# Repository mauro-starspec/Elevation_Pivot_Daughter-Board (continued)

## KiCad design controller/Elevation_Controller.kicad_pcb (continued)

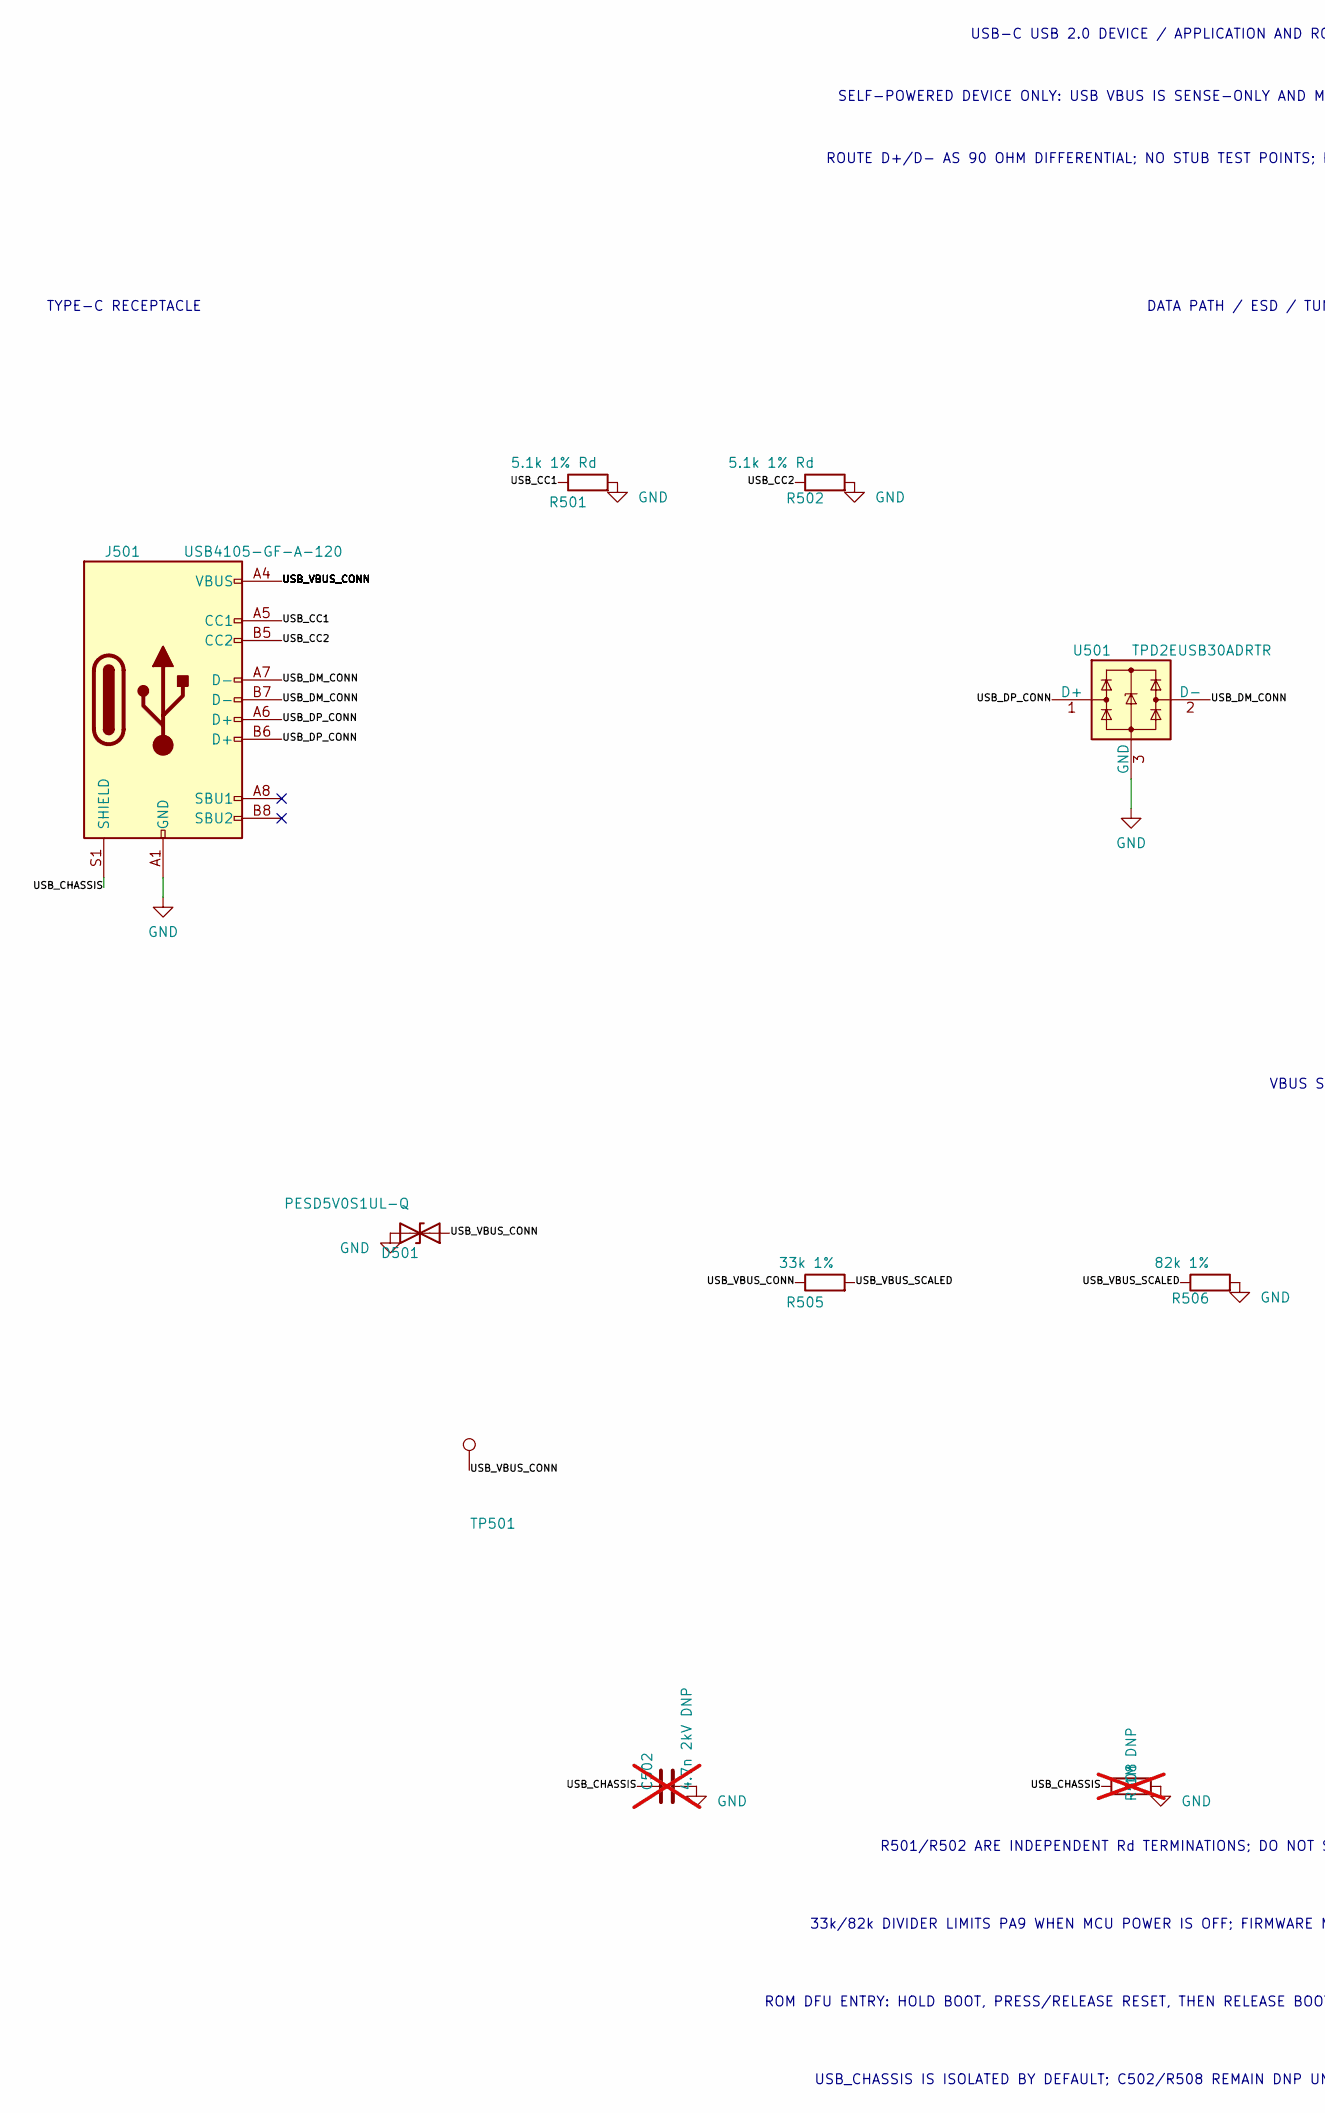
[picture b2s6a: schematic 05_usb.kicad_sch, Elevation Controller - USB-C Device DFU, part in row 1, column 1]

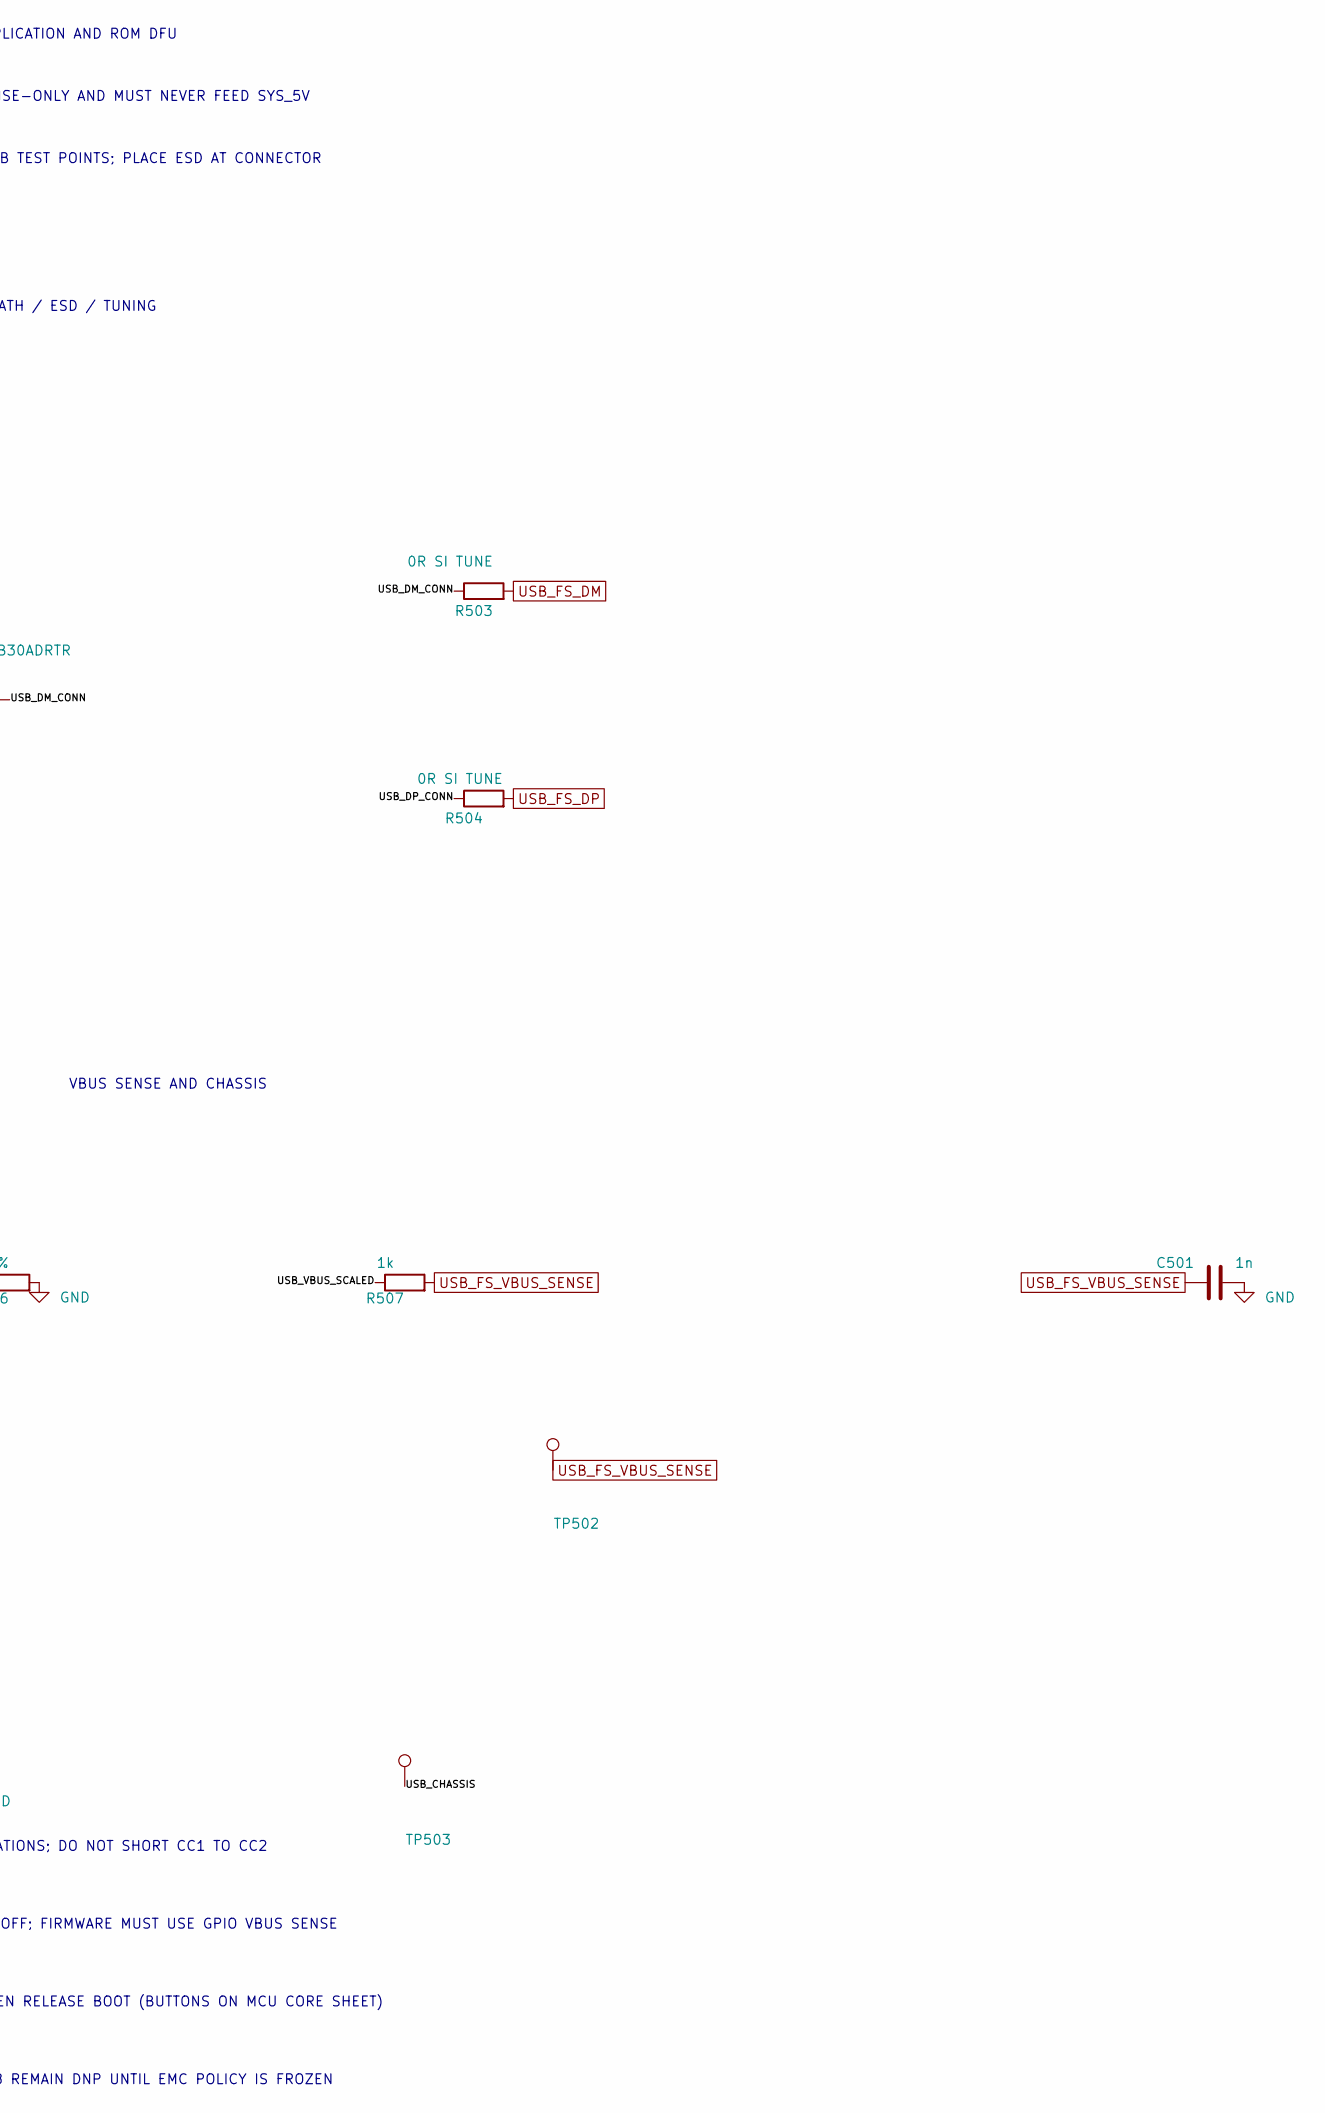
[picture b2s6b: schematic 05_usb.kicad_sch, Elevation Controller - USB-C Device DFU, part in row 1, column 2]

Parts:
C501: 1n; C_0805_2012Metric; Voltage 50V; MPN C0805C102J5GACTU; LCSC Part # C2167084
C502: 4.7n 2kV DNP; C_1812_4532Metric; MPN NOT SELECTED - DNP; LCSC Part # NOT_SELECTED; not fitted
D501: PESD5V0S1UL-Q; D_SOD-882; MPN PESD5V0S1UL-QYL; LCSC Part # C20235797
J501: USB4105-GF-A-120; USB_C_Receptacle_GCT_USB4105-xx-A_16P_TopMnt_Horizontal; MPN USB4105-GF-A-120; LCSC Part # C5184243
R501, R502: 5.1k 1% Rd; R_0805_2012Metric; MPN CRCW08055K10FKEA; LCSC Part # C844854
R503, R504: 0R SI TUNE; R_0805_2012Metric; MPN CRCW08050000Z0EA; LCSC Part # C844934
R505: 33k 1%; R_0805_2012Metric; MPN CRCW080533K0FKEA; LCSC Part # C242487
R506: 82k 1%; R_0805_2012Metric; MPN CRCW080582K0FKEA; LCSC Part # NOT_LISTED
R507: 1k; R_0805_2012Metric; MPN CRCW08051K00FKEA; LCSC Part # C844939
R508: 1M DNP; R_0805_2012Metric; MPN NOT SELECTED - DNP; LCSC Part # NOT_SELECTED; not fitted
TP501: USB_VBUS_CONN; TestPoint_Pad_D2.0mm; MPN N/A; LCSC Part # N/A
TP502: USB_FS_VBUS_SENSE; TestPoint_Pad_D2.0mm; MPN N/A; LCSC Part # N/A
TP503: USB_CHASSIS; TestPoint_Pad_D2.0mm; MPN N/A; LCSC Part # N/A
U501: TPD2EUSB30ADRTR; Texas_DRT-3; MPN TPD2EUSB30ADRTR; LCSC Part # C94934

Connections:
/USB-C/USB_CC1: J501.A5 (CC1), R501.1
/USB-C/USB_CC2: J501.B5 (CC2), R502.1
/USB-C/USB_CHASSIS: C502.1, J501.S1 (SHIELD), R508.1, TP503.1
/USB-C/USB_DM_CONN: J501.A7 (D-), J501.B7 (D-), R503.1, U501.2 (D-)
/USB-C/USB_DP_CONN: J501.A6 (D+), J501.B6 (D+), R504.1, U501.1 (D+)
/USB-C/USB_VBUS_CONN: D501.1 (A1), J501.A4 (VBUS), J501.A9 (VBUS), J501.B4 (VBUS), J501.B9 (VBUS), R505.1, TP501.1
/USB-C/USB_VBUS_SCALED: R505.2, R506.1, R507.1
GND: C501.2, C502.2, D501.2 (A2), J501.A1 (GND), J501.A12 (GND), J501.B1 (GND), J501.B12 (GND), R501.2, R502.2, R506.2, R508.2, U501.3 (GND); also elsewhere on the board
USB_FS_DM: R503.2; also elsewhere on the board
USB_FS_DP: R504.2; also elsewhere on the board
USB_FS_VBUS_SENSE: C501.1, R507.2, TP502.1; also elsewhere on the board

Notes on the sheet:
33k/82k DIVIDER LIMITS PA9 WHEN MCU POWER IS OFF; FIRMWARE MUST USE GPIO VBUS SENSE
DATA PATH / ESD / TUNING
VBUS SENSE AND CHASSIS
ROUTE D+/D- AS 90 OHM DIFFERENTIAL; NO STUB TEST POINTS; PLACE ESD AT CONNECTOR
TYPE-C RECEPTACLE
R501/R502 ARE INDEPENDENT Rd TERMINATIONS; DO NOT SHORT CC1 TO CC2
SELF-POWERED DEVICE ONLY: USB VBUS IS SENSE-ONLY AND MUST NEVER FEED SYS_5V
USB-C USB 2.0 DEVICE / APPLICATION AND ROM DFU
ROM DFU ENTRY: HOLD BOOT, PRESS/RELEASE RESET, THEN RELEASE BOOT (BUTTONS ON MCU CORE SHEET)
USB_CHASSIS IS ISOLATED BY DEFAULT; C502/R508 REMAIN DNP UNTIL EMC POLICY IS FROZEN

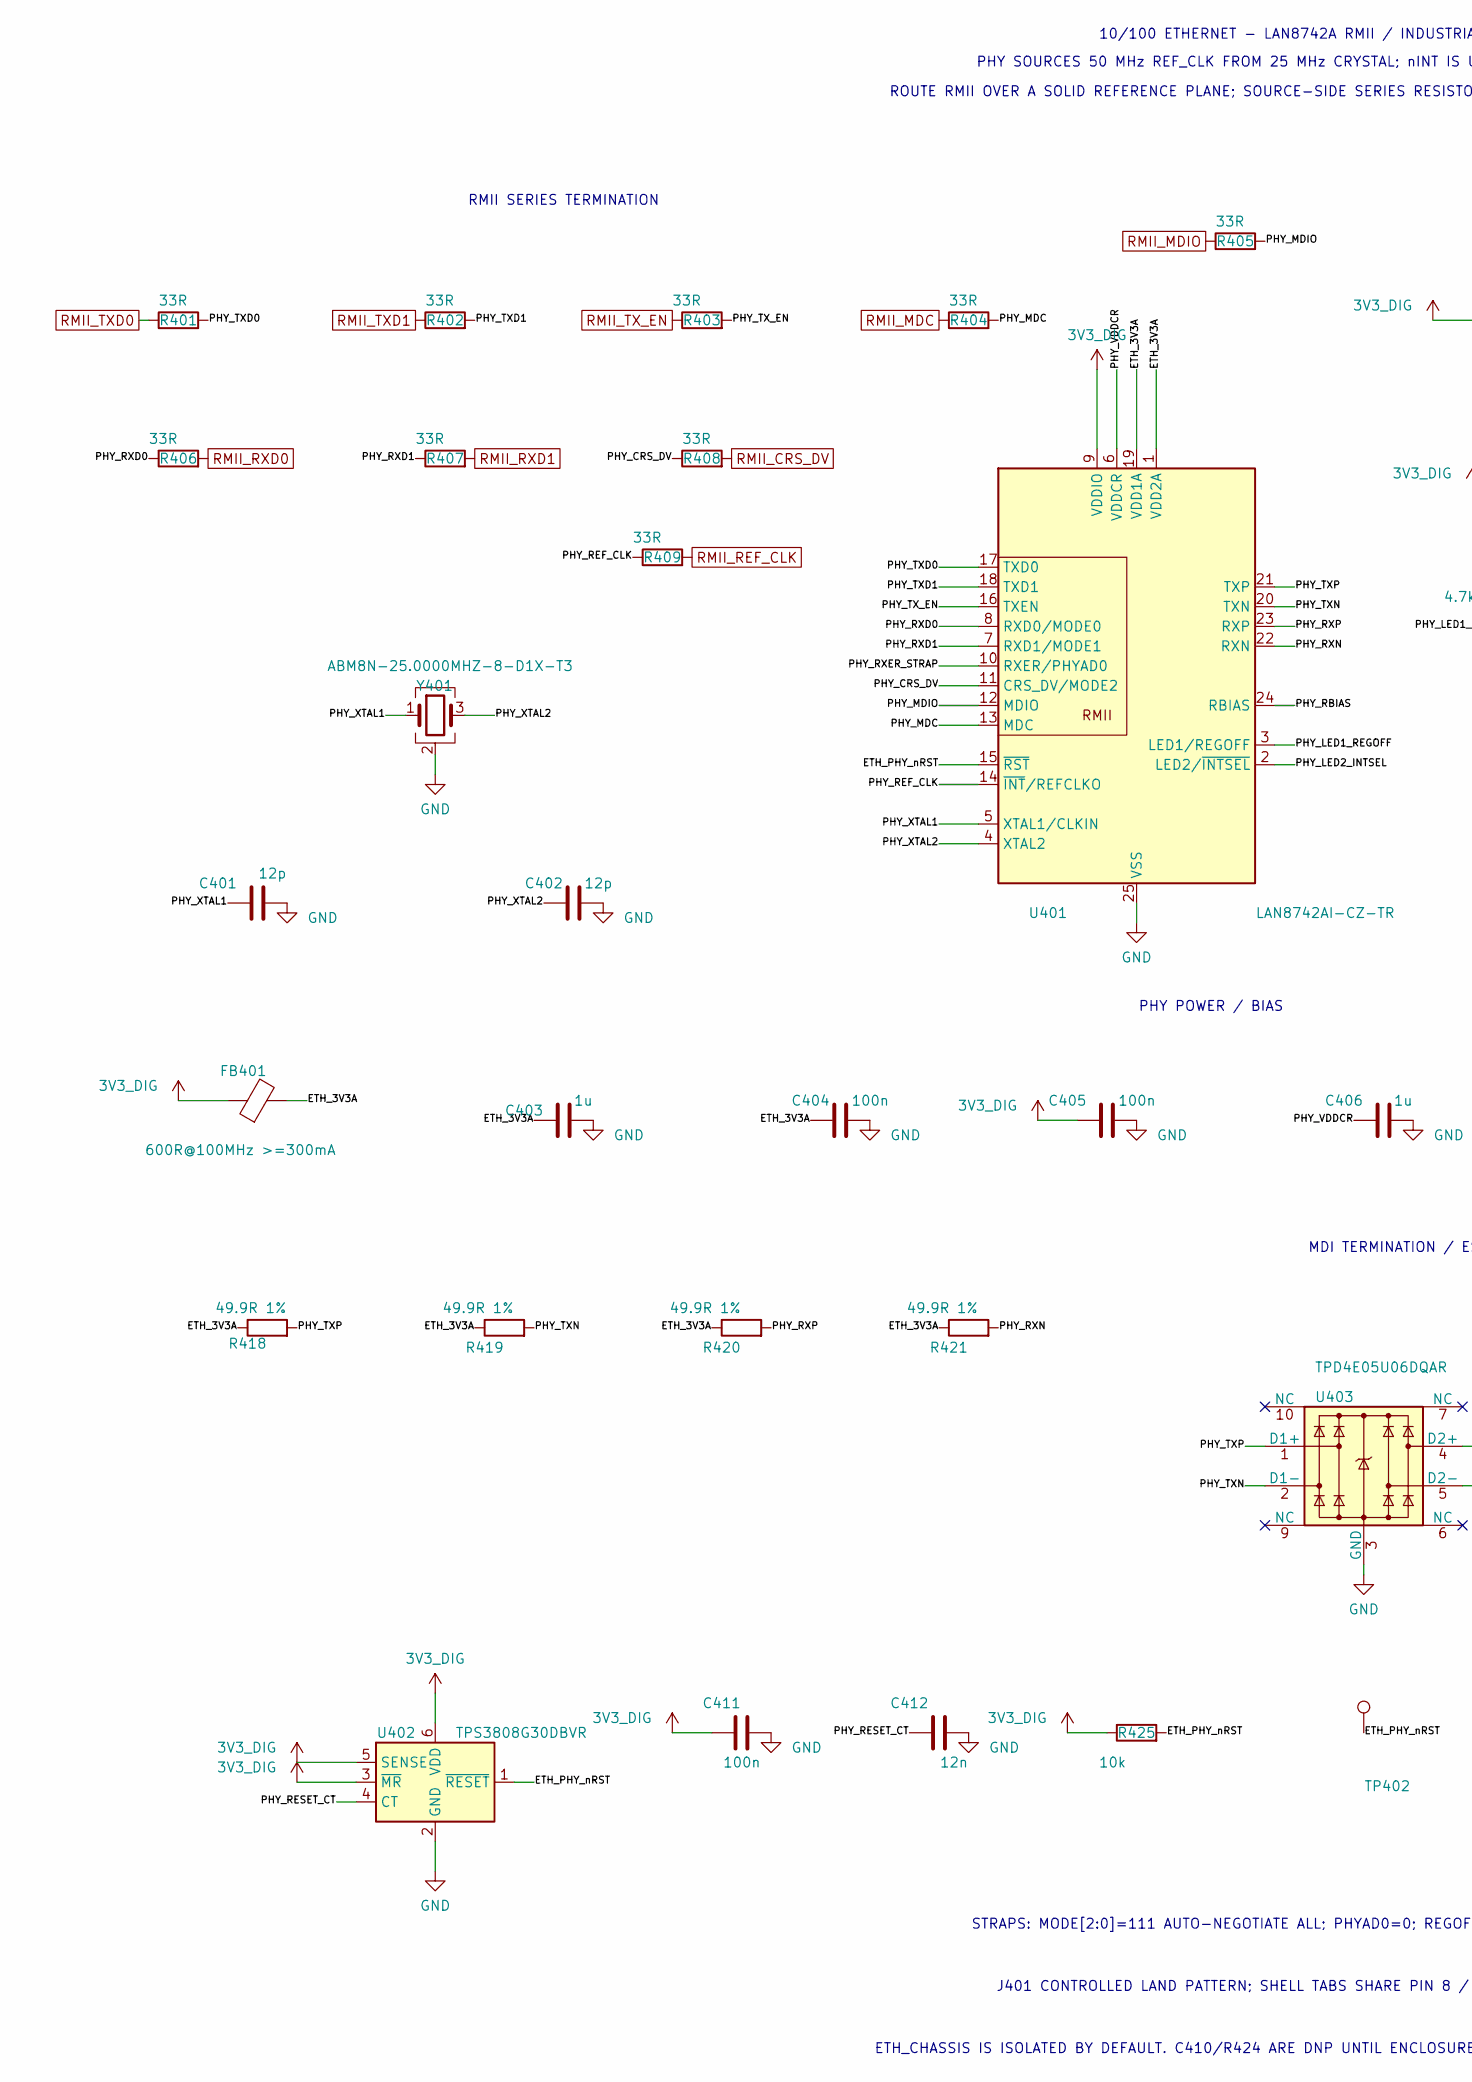
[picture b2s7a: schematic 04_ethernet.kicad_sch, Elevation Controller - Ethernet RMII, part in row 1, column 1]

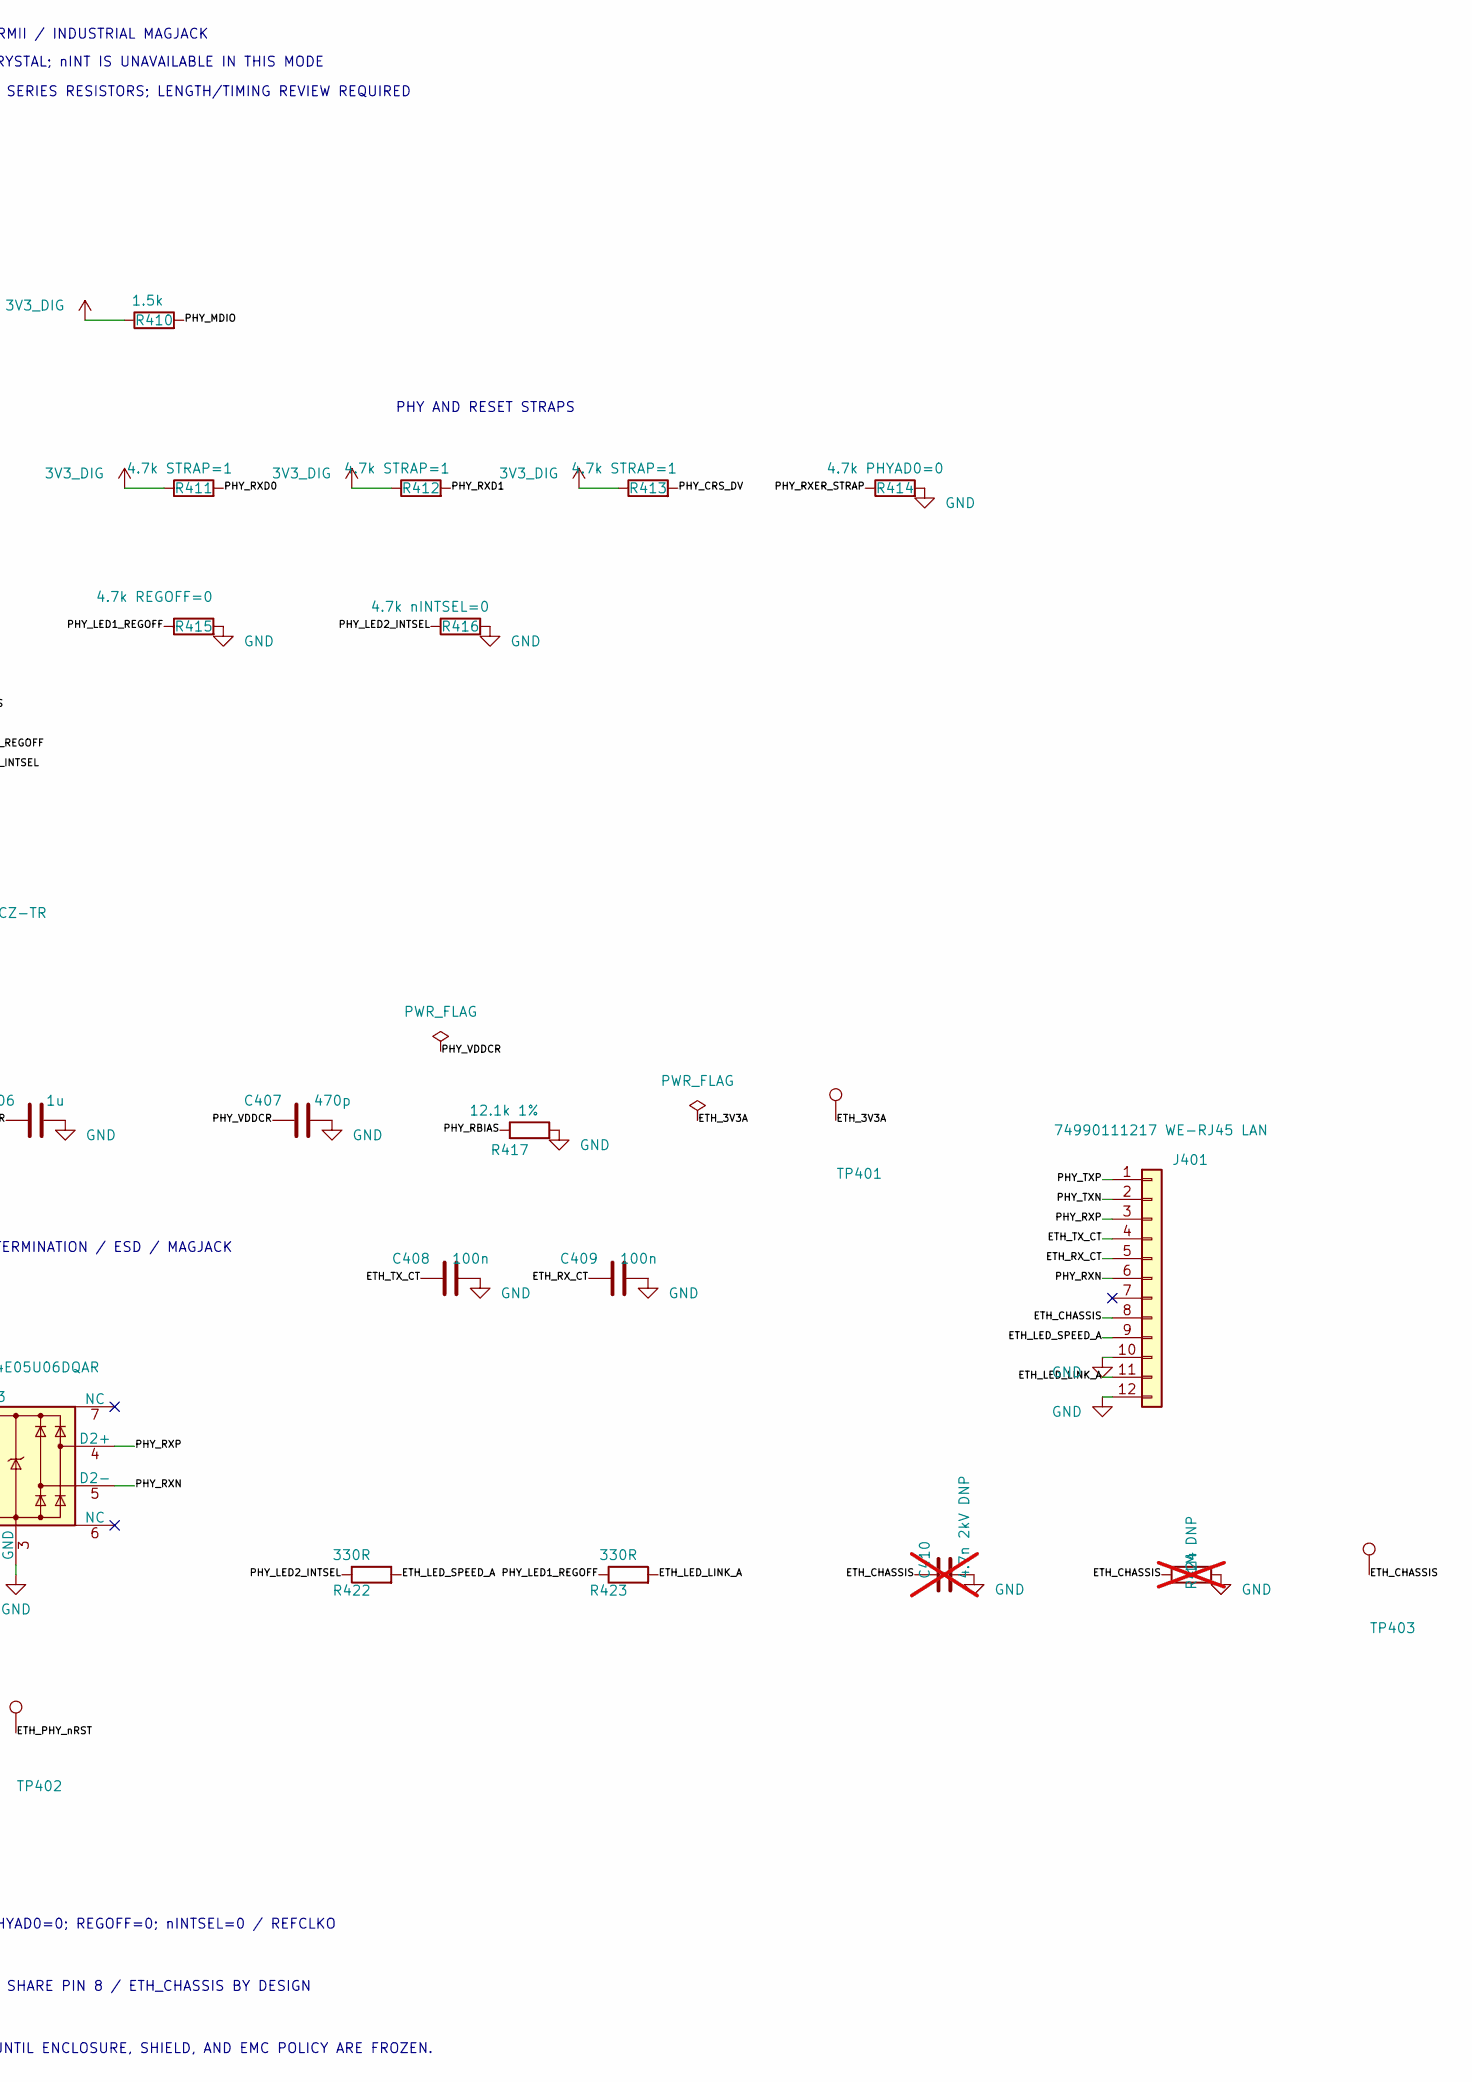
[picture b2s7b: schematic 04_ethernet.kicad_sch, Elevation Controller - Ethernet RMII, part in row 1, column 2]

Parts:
C401, C402: 12p; C_0805_2012Metric; Voltage 50V; MPN C0805C120J5GACTU; LCSC Part # C2168859
C403, C406: 1u; C_0805_2012Metric; Voltage 25V; MPN C2012X7R1E105K085AB; LCSC Part # NOT_LISTED
C404, C405, C408, C409, C411: 100n; C_0805_2012Metric; Voltage 50V; MPN C0805C104K5RACTU; LCSC Part # C3018562
C407: 470p; C_0805_2012Metric; Voltage 50V; MPN C0805C471J5GACTU; LCSC Part # NOT_LISTED
C410: 4.7n 2kV DNP; C_1812_4532Metric; MPN NOT SELECTED - DNP; LCSC Part # NOT_SELECTED; not fitted
C412: 12n; C_0805_2012Metric; Voltage 50V; MPN C0805C123K5RACTU; LCSC Part # NOT_LISTED
FB401: 600R@100MHz >=300mA; L_0805_2012Metric; MPN BLM21PG601SN1D; LCSC Part # C41556732
J401: 74990111217 WE-RJ45 LAN; Wurth_74990111217_WE-RJ45LAN; MPN 74990111217; LCSC Part # NOT_LISTED
R401, R402, R403, R404, R405, R406, R407, R408, R409: 33R; R_0805_2012Metric; MPN CRCW080533R0FKEA; LCSC Part # C844840
R410: 1.5k; R_0805_2012Metric; MPN CRCW08051K50FKEA; LCSC Part # C844824
R411, R412, R413: 4.7k STRAP=1; R_0805_2012Metric; MPN CRCW08054K70FKEA; LCSC Part # C844941
R414: 4.7k PHYAD0=0; R_0805_2012Metric; MPN CRCW08054K70FKEA; LCSC Part # C844941
R415: 4.7k REGOFF=0; R_0805_2012Metric; MPN CRCW08054K70FKEA; LCSC Part # C844941
R416: 4.7k nINTSEL=0; R_0805_2012Metric; MPN CRCW08054K70FKEA; LCSC Part # C844941
R417: 12.1k 1%; R_0805_2012Metric; MPN CRCW080512K1FKEA; LCSC Part # C844198
R418, R419, R420, R421: 49.9R 1%; R_0805_2012Metric; MPN CRCW080549R9FKEA; LCSC Part # C844847
R422, R423: 330R; R_0805_2012Metric; MPN CRCW0805330RFKEA; LCSC Part # C844839
R424: 1M DNP; R_0805_2012Metric; MPN NOT SELECTED - DNP; LCSC Part # NOT_SELECTED; not fitted
R425: 10k; R_0805_2012Metric; MPN CRCW080510K0FKEA; LCSC Part # C844937
TP401: ETH_3V3A; TestPoint_Pad_D2.0mm; MPN N/A; LCSC Part # N/A
TP402: ETH_PHY_nRST; TestPoint_Pad_D2.0mm; MPN N/A; LCSC Part # N/A
TP403: ETH_CHASSIS; TestPoint_Pad_D2.0mm; MPN N/A; LCSC Part # N/A
U401: LAN8742AI-CZ-TR; QFN-24-1EP_4x4mm_P0.5mm_EP2.6x2.6mm_ThermalVias; MPN LAN8742AI-CZ-TR; LCSC Part # C621425
U402: TPS3808G30DBVR; SOT-23-6; MPN TPS3808G30DBVR; LCSC Part # C189211
U403: TPD4E05U06DQAR; USON-10_2.5x1.0mm_P0.5mm; MPN TPD4E05U06DQAR; LCSC Part # C22390021
Y401: ABM8N-25.0000MHZ-8-D1X-T3; Crystal_SMD_3225-4Pin_3.2x2.5mm; MPN ABM8N-25.0000MHZ-8-D1X-T3; LCSC Part # NOT_LISTED

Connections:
3V3_DIG: C405.1, C411.1, FB401.1, R410.1, R411.1, R412.1, R413.1, R425.1, U401.9 (VDDIO), U402.3 (~MR), U402.5 (SENSE), U402.6 (VDD); also elsewhere on the board
/Ethernet/ETH_3V3A: C403.1, C404.1, FB401.2, R418.1, R419.1, R420.1, R421.1, TP401.1, U401.1 (VDD2A), U401.19 (VDD1A)
/Ethernet/ETH_CHASSIS: C410.1, J401.8, R424.1, TP403.1
/Ethernet/ETH_LED_LINK_A: J401.11, R423.2
/Ethernet/ETH_LED_SPEED_A: J401.9, R422.2
/Ethernet/ETH_PHY_nRST: R425.2, TP402.1, U401.15 (~RST), U402.1 (~RESET)
/Ethernet/ETH_RX_CT: C409.1, J401.5
/Ethernet/ETH_TX_CT: C408.1, J401.4
/Ethernet/PHY_CRS_DV: R408.1, R413.2, U401.11 (CRS_DV/MODE2)
/Ethernet/PHY_LED1_REGOFF: R415.1, R423.1, U401.3 (LED1/REGOFF)
/Ethernet/PHY_LED2_INTSEL: R416.1, R422.1, U401.2 (LED2/~INTSEL)
/Ethernet/PHY_MDC: R404.2, U401.13 (MDC)
/Ethernet/PHY_MDIO: R405.2, R410.2, U401.12 (MDIO)
/Ethernet/PHY_RBIAS: R417.1, U401.24 (RBIAS)
/Ethernet/PHY_REF_CLK: R409.1, U401.14 (~INT/REFCLKO)
/Ethernet/PHY_RESET_CT: C412.1, U402.4 (CT)
/Ethernet/PHY_RXD0: R406.1, R411.2, U401.8 (RXD0/MODE0)
/Ethernet/PHY_RXD1: R407.1, R412.2, U401.7 (RXD1/MODE1)
/Ethernet/PHY_RXER_STRAP: R414.1, U401.10 (RXER/PHYAD0)
/Ethernet/PHY_RXN: J401.6, R421.2, U401.22 (RXN), U403.5 (D2-)
/Ethernet/PHY_RXP: J401.3, R420.2, U401.23 (RXP), U403.4 (D2+)
/Ethernet/PHY_TXD0: R401.2, U401.17 (TXD0)
/Ethernet/PHY_TXD1: R402.2, U401.18 (TXD1)
/Ethernet/PHY_TXN: J401.2, R419.2, U401.20 (TXN), U403.2 (D1-)
/Ethernet/PHY_TXP: J401.1, R418.2, U401.21 (TXP), U403.1 (D1+)
/Ethernet/PHY_TX_EN: R403.2, U401.16 (TXEN)
/Ethernet/PHY_VDDCR: C406.1, C407.1, U401.6 (VDDCR)
/Ethernet/PHY_XTAL1: C401.1, U401.5 (XTAL1/CLKIN), Y401.1
/Ethernet/PHY_XTAL2: C402.1, U401.4 (XTAL2), Y401.3
GND: C401.2, C402.2, C403.2, C404.2, C405.2, C406.2, C407.2, C408.2, C409.2, C410.2, C411.2, C412.2, J401.10, J401.12, R414.2, R415.2, R416.2, R417.2, R424.2, U401.25 (VSS), U402.2 (GND), U403.3 (GND), U403.8 (GND), Y401.2 (G), Y401.4 (G); also elsewhere on the board
RMII_CRS_DV: R408.2; also elsewhere on the board
RMII_MDC: R404.1; also elsewhere on the board
RMII_MDIO: R405.1; also elsewhere on the board
RMII_REF_CLK: R409.2; also elsewhere on the board
RMII_RXD0: R406.2; also elsewhere on the board
RMII_RXD1: R407.2; also elsewhere on the board
RMII_TXD0: R401.1; also elsewhere on the board
RMII_TXD1: R402.1; also elsewhere on the board
RMII_TX_EN: R403.1; also elsewhere on the board

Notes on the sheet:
ETH_CHASSIS IS ISOLATED BY DEFAULT. C410/R424 ARE DNP UNTIL ENCLOSURE, SHIELD, AND EMC POLICY ARE FROZEN.
10/100 ETHERNET - LAN8742A RMII / INDUSTRIAL MAGJACK
ROUTE RMII OVER A SOLID REFERENCE PLANE; SOURCE-SIDE SERIES RESISTORS; LENGTH/TIMING REVIEW REQUIRED
PHY POWER / BIAS
J401 CONTROLLED LAND PATTERN; SHELL TABS SHARE PIN 8 / ETH_CHASSIS BY DESIGN
RMII SERIES TERMINATION
PHY AND RESET STRAPS
PHY SOURCES 50 MHz REF_CLK FROM 25 MHz CRYSTAL; nINT IS UNAVAILABLE IN THIS MODE
MDI TERMINATION / ESD / MAGJACK
STRAPS: MODE[2:0]=111 AUTO-NEGOTIATE ALL; PHYAD0=0; REGOFF=0; nINTSEL=0 / REFCLKO

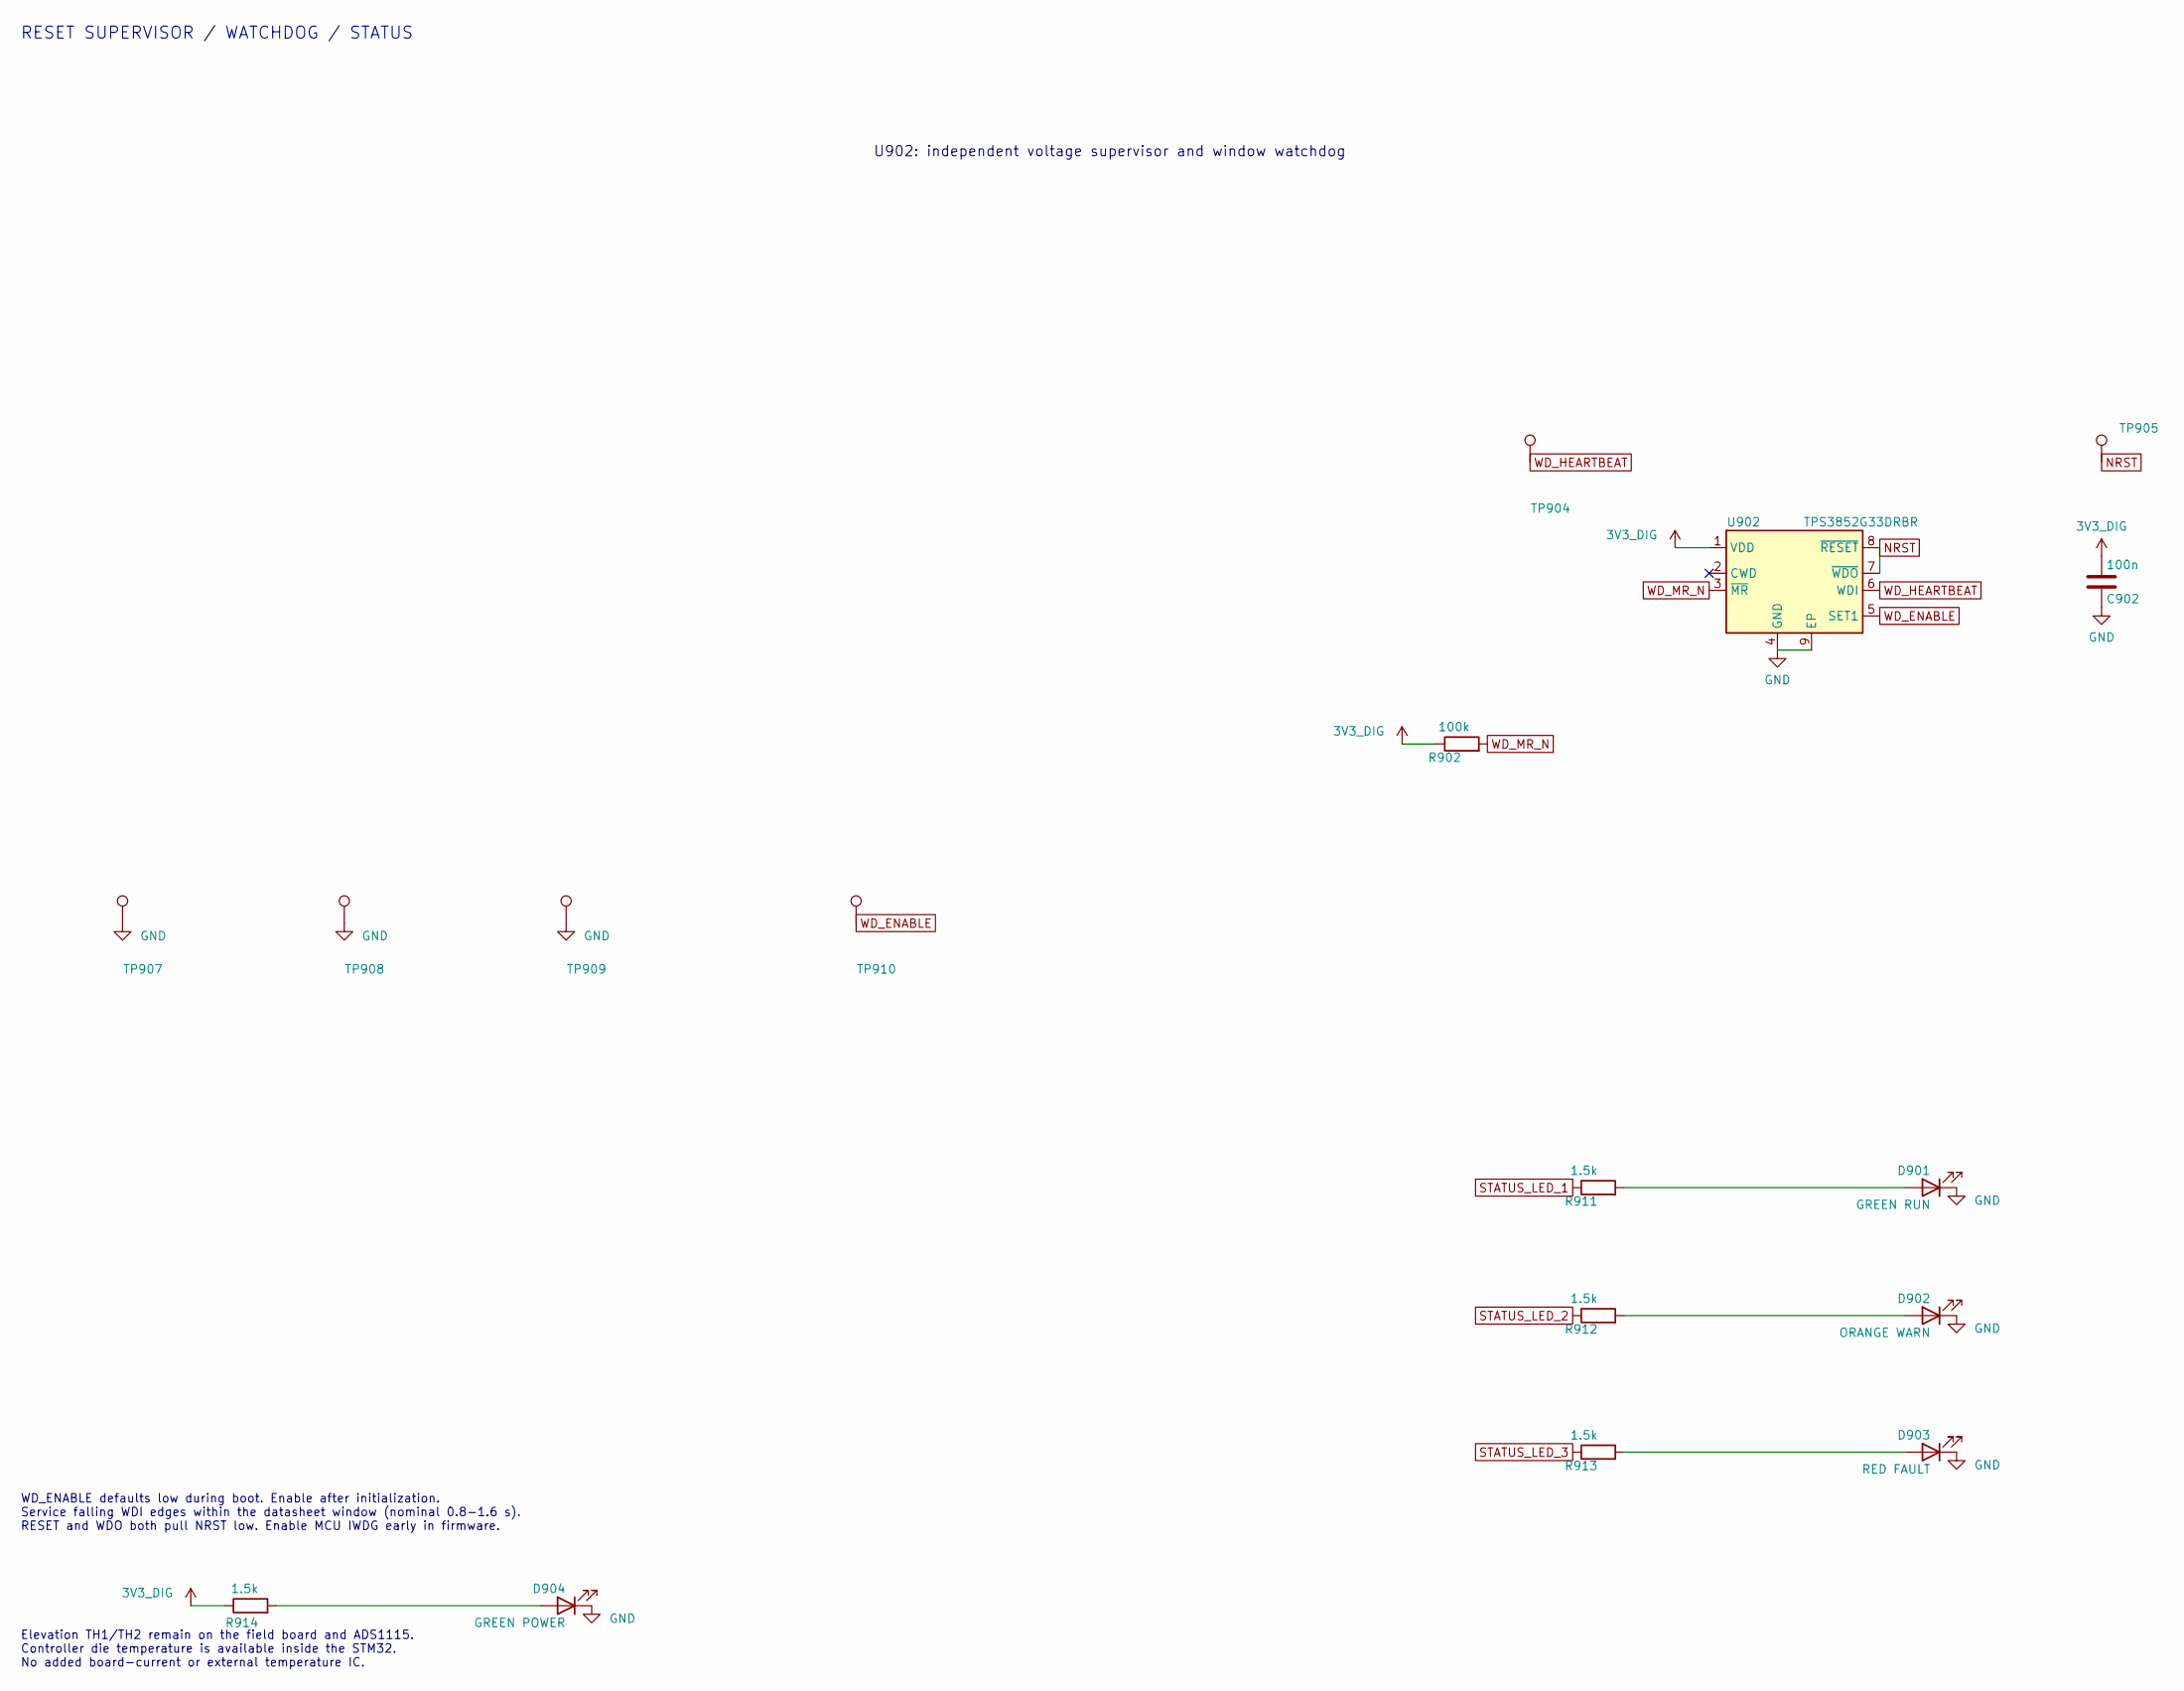
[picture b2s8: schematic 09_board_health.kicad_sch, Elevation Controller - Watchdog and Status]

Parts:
C902: 100n; C_0805_2012Metric; Voltage 50V; MPN C0805C104K5RACTU; LCSC Part # C3018562
D901: GREEN RUN; LED_0805_2012Metric; MPN APT2012SGC; LCSC Part # C5353439
D902: ORANGE WARN; LED_0805_2012Metric; MPN APT2012SEC/J4-PRV; LCSC Part # NOT_LISTED
D903: RED FAULT; LED_0805_2012Metric; MPN APT2012SRCPRV; LCSC Part # NOT_LISTED
D904: GREEN POWER; LED_0805_2012Metric; MPN APT2012SGC; LCSC Part # C5353439
R902: 100k; R_0805_2012Metric; MPN CRCW0805100KFKEA; LCSC Part # C844935
R911, R912, R913, R914: 1.5k; R_0805_2012Metric; MPN CRCW08051K50FKEA; LCSC Part # C844824
TP904: WD_HEARTBEAT; TestPoint_Pad_D2.0mm; MPN N/A; LCSC Part # N/A
TP905: NRST; TestPoint_Pad_D2.0mm; MPN N/A; LCSC Part # N/A
TP907, TP908, TP909: GND; TestPoint_Pad_D2.0mm; MPN N/A; LCSC Part # N/A
TP910: WD_ENABLE; TestPoint_Pad_D2.0mm; MPN N/A; LCSC Part # N/A
U902: TPS3852G33DRBR; TI_DRB0008A_TPS3852; MPN TPS3852G33DRBR; LCSC Part # NOT_LISTED

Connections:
3V3_DIG: C902.1, R902.1, R914.1, U902.1 (VDD); also elsewhere on the board
GND: C902.2, D901.1 (K), D902.1 (K), D903.1 (K), D904.1 (K), TP907.1, TP908.1, TP909.1, U902.4 (GND), U902.9 (EP); also elsewhere on the board
NRST: TP905.1, U902.7 (~WDO), U902.8 (~RESET); also elsewhere on the board
unnamed: D901.2 (A), R911.2
unnamed: D902.2 (A), R912.2
unnamed: D903.2 (A), R913.2
unnamed: D904.2 (A), R914.2
STATUS_LED_1: R911.1; also elsewhere on the board
STATUS_LED_2: R912.1; also elsewhere on the board
STATUS_LED_3: R913.1; also elsewhere on the board
WD_ENABLE: TP910.1, U902.5 (SET1); also elsewhere on the board
WD_HEARTBEAT: TP904.1, U902.6 (WDI); also elsewhere on the board
WD_MR_N: R902.2, U902.3 (~MR)

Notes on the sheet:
WD_ENABLE defaults low during boot. Enable after initialization. Service falling WDI edges within the datasheet window (nominal 0.8-1.6 s). RESET and WDO both pull NRST low. Enable MCU IWDG early in firmware.
RESET SUPERVISOR / WATCHDOG / STATUS
U902: independent voltage supervisor and window watchdog
Elevation TH1/TH2 remain on the field board and ADS1115. Controller die temperature is available inside the STM32. No added board-current or external temperature IC.

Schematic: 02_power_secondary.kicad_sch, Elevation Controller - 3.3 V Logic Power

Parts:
C211: 10u; C_1206_3216Metric; Voltage 25V; MPN C1206C106K3RACTU; LCSC Part # C2168111
C212: 220n; C_0805_2012Metric; Voltage 50V; MPN C0805C224K5RACTU; LCSC Part # C2167160
C213, C221: 1u; C_0805_2012Metric; Voltage 25V; MPN C2012X7R1E105K085AB; LCSC Part # NOT_LISTED
C214: 100n; C_0805_2012Metric; Voltage 50V; MPN C0805C104K5RACTU; LCSC Part # C3018562
C215, C216, C217, C218: 22u; C_1210_3225Metric; Voltage 25V; MPN C1210C226K3RACTU; LCSC Part # C22411650
C222: 100n; C_0805_2012Metric; Voltage 50V; MPN C0805C104K5RACTU; JLCPCB Status Historical ID; recheck exact part and a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
FB201: BLM21PG221SN1D; L_0805_2012Metric; MPN BLM21PG221SN1D; JLCPCB Library UNVERIFIED
L201: XGL5030-682MEC 6.8uH; Coilcraft_XGL5030; MPN XGL5030-682MEC; LCSC Part # NOT_LISTED
R211: 100k 0.1%; R_0805_2012Metric; MPN TNPW0805100KBEEA; LCSC Part # C3034987
R212: 43.2k 0.1%; R_0805_2012Metric; MPN TNPW080543K2BEEA; LCSC Part # NOT_LISTED
R213: 100k; R_0805_2012Metric; MPN CRCW0805100KFKEA; LCSC Part # C844935
TP201: SYS_5V; TestPoint_Pad_D2.0mm; MPN N/A; LCSC Part # N/A
TP211: 3V3_DIG; TestPoint_Pad_D2.0mm; MPN N/A; LCSC Part # N/A
TP212: 3V3_DIG_PG; TestPoint_Pad_D2.0mm; MPN N/A; LCSC Part # N/A
U202: LMR33630ADDAR; SOIC-8-1EP_3.9x4.9mm_P1.27mm_EP2.29x3mm; MPN LMR33630ADDAR; LCSC Part # C841384

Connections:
3V3_ANA: C221.1, C222.1, FB201.2; also elsewhere on the board
3V3_DIG: C215.1, C216.1, C217.1, C218.1, FB201.1, L201.2, R211.1, R213.1, TP211.1; also elsewhere on the board
3V3_DIG_PG: R213.2, TP212.1, U202.4 (PG)
GND: C211.2, C212.2, C213.2, C215.2, C216.2, C217.2, C218.2, C221.2, C222.2, R212.2, U202.1 (GND), U202.9 (GND); also elsewhere on the board
LMR_BOOT: C214.1, U202.7 (BOOT)
LMR_FB: R211.2, R212.1, U202.5 (FB)
LMR_SW: C214.2, L201.1, U202.8 (SW)
LMR_VCC: C213.1, U202.6 (VCC)
SYS_5V: C211.1, C212.1, TP201.1, U202.2 (VIN), U202.3 (EN); also elsewhere on the board

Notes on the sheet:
3.3 V CONTROLLER AND ELEVATION LOGIC POWER
U202: 5 V to 3.3 V buck regulator
MCU ANALOG SUPPLY FILTER
FB201: 220 ohm at 100 MHz ferrite bead. VDDA/VREF local capacitors and R5 remain on MCU sheet. No external analog channels or analog supply export.
3V3_DIG feeds MCU, PHY, USB supply and elevation isolator logic through J30. Both boards share this rail; no separate switched 3.3 V domain across signal pins.
